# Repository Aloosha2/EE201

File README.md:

# EE 201

This is contains all of my content for lab 8: arduometer

***NOTE: my voltage divider was faulty so I asked Pranav how to proceed with assignment. After many tests and checks, my board would not connect to the arduino and code would not upload. Pranav and Sushree said the board was too damaged so I should just proceed with building the case. Thus, here are the photos in the branch.

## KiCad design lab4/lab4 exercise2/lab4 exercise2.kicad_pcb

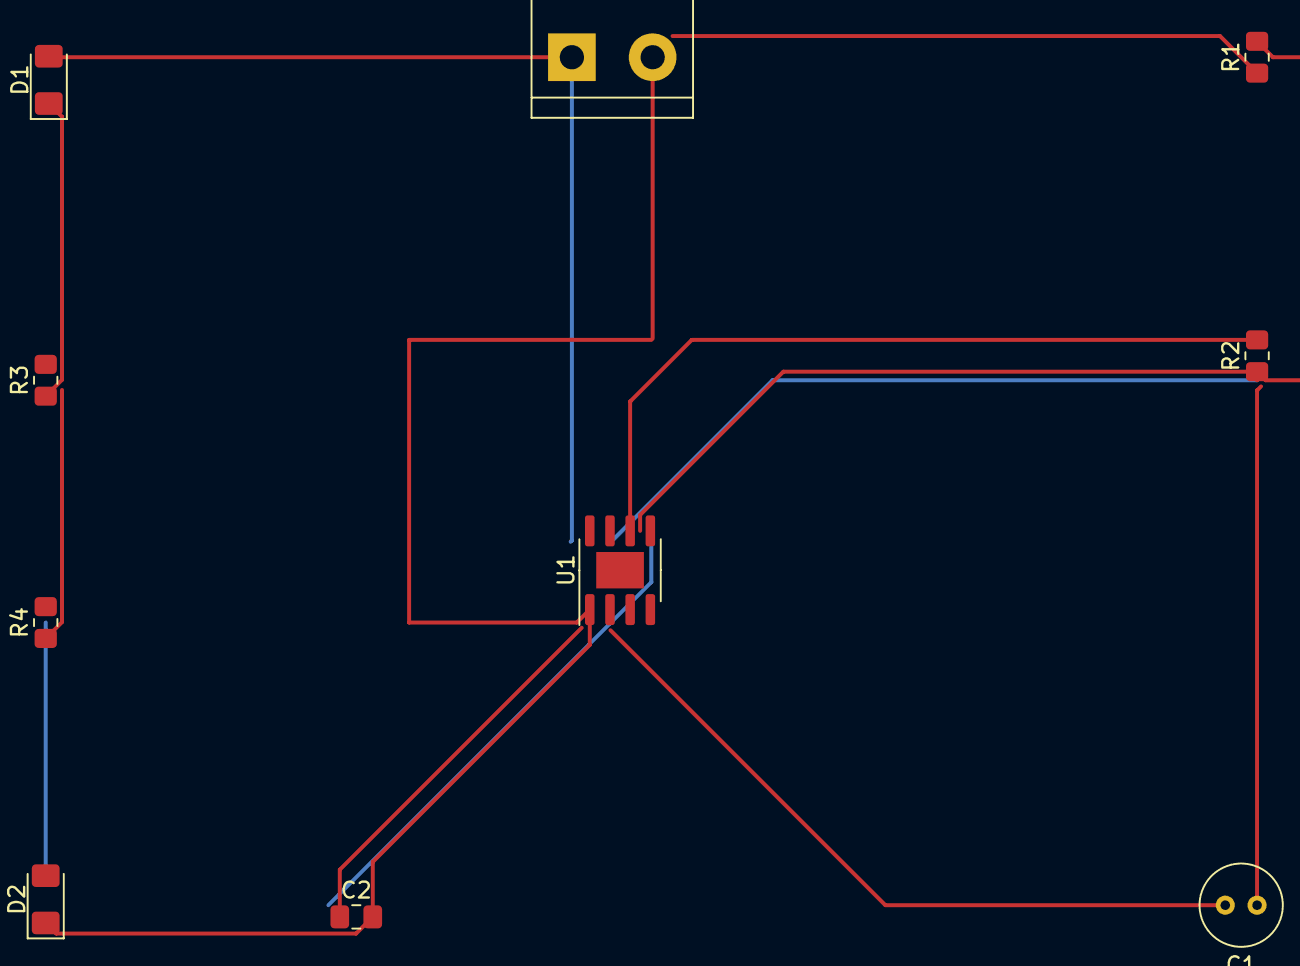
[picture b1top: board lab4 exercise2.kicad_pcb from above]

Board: 2 copper layers, 10 parts (0 on the bottom side), 8 nets.

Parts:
C1: 10 µF; C_Radial_D5.0mm_H5.0mm_P2.00mm
C2: 0.01µF; C_0805_2012Metric_Pad1.18x1.45mm_HandSolder
D1, D2: LED; LED_1206_3216Metric_Pad1.42x1.75mm_HandSolder
J1: Conn_01x02_Male; TerminalBlock_bornier-2_P5.08mm
R1, R3, R4: 1k; R_0805_2012Metric_Pad1.20x1.40mm_HandSolder
R2: 10k; R_0805_2012Metric_Pad1.20x1.40mm_HandSolder
U1: NE555D; SOIC-8-1EP_3.9x4.9mm_P1.27mm_EP2.29x3mm

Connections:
+9V: D1.2 (A), J1.1, R1.1, U1.8 (VCC)
GND: C1.2, C2.2, D2.1 (K), J1.2, U1.1 (GND)
unnamed: C1.1, R2.2, U1.6 (THR)
unnamed: C2.1, U1.5 (CV)
unnamed: D1.1 (K), R3.1
unnamed: D2.2 (A), R4.2
unnamed: R1.2, R2.1, U1.7 (DIS)
unnamed: R3.2, R4.1

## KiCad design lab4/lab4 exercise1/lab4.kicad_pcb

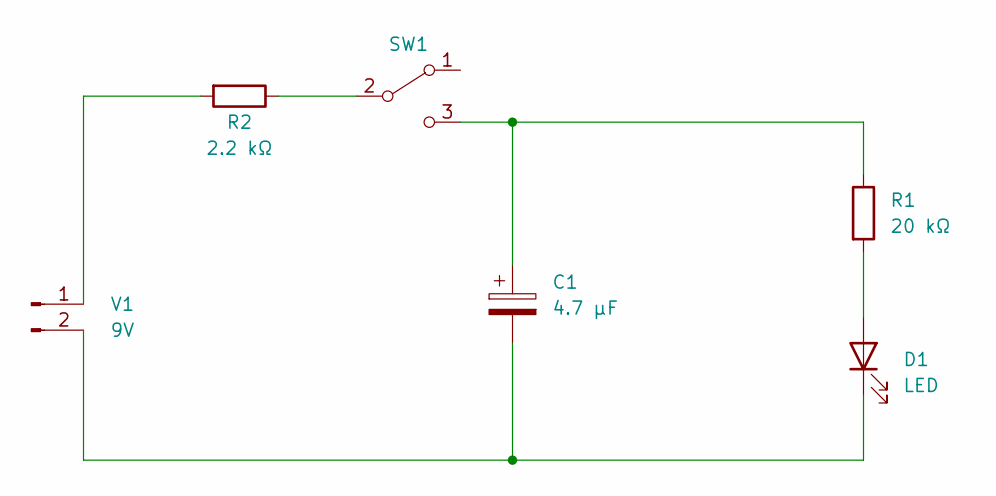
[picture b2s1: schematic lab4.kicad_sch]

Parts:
C1: 4.7 µF; C_Radial_D5.0mm_H5.0mm_P2.00mm
D1: LED; LED_D5.0mm
R1: 20 kΩ; R_Axial_DIN0516_L15.5mm_D5.0mm_P20.32mm_Horizontal
R2: 2.2 kΩ; R_Axial_DIN0516_L15.5mm_D5.0mm_P20.32mm_Horizontal
SW1: s; SW_E-Switch_EG1224_SPDT_Angled
V1: 9V; JST_PH_B2B-PH-K_1x02_P2.00mm_Vertical

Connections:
unnamed: C1.1, R1.1, SW1.3 (C)
unnamed: C1.2, D1.1 (K), V1.2
unnamed: D1.2 (A), R1.2
unnamed: R2.1, SW1.2 (B)
unnamed: R2.2, V1.1

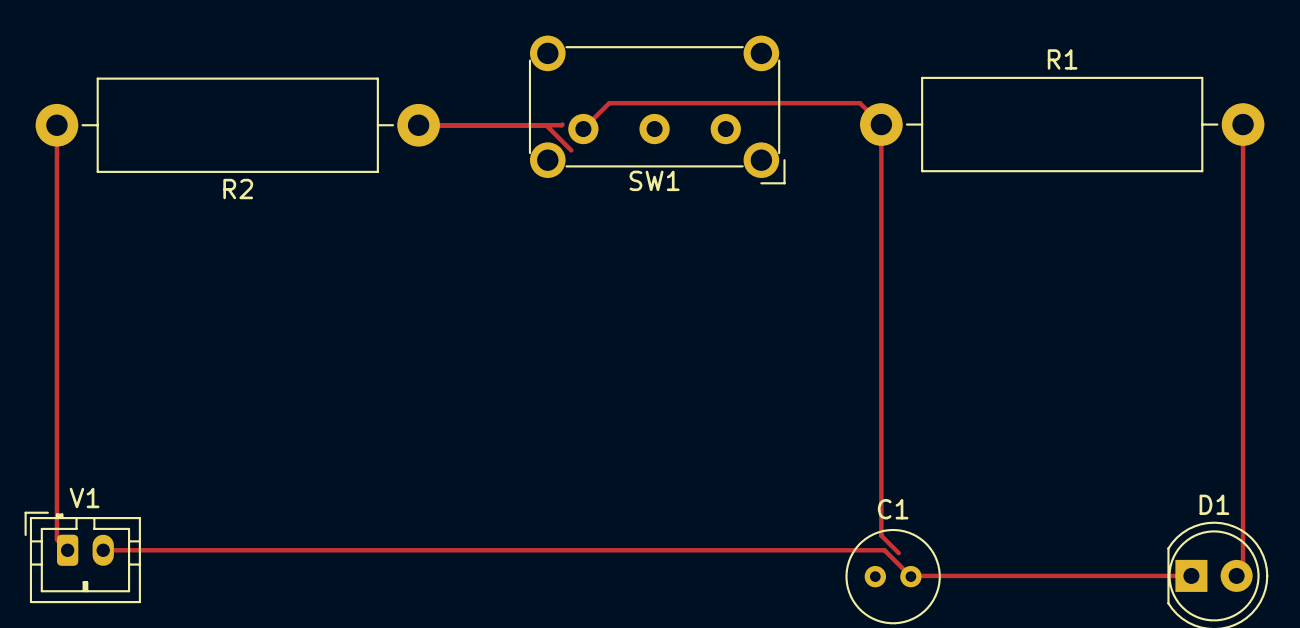
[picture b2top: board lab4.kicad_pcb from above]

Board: 2 copper layers, 6 parts (0 on the bottom side), 5 nets.

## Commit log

2023-01-10 Created the heading
2023-01-10 Adding name.txt
2023-01-10 added a second line
2023-01-10 added aboutMe
2023-01-10 added file
2023-01-10 add readme
2023-01-10 updated readme file
2023-01-10 added photo
2023-01-11 updated final readMe
2023-01-11 Adding a file.
2023-01-19 created new branch
2023-01-19 added lab1
2023-01-19 added Arduino exercises
2023-01-24 added read me file to lab 4
2023-01-24 added files
2023-01-24 added lab4
2023-01-24 lab4 work
2023-01-24 lab 4 work
2023-01-31 uploaded photos
2023-01-31 removed lab4
2023-02-01 added soldering photos
2023-02-07 updated lab4 from lab6 instructions
2023-02-07 lab6 work on lab4
2023-02-14 created gerber files
2023-02-14 added gerber files
2023-03-09 Updated lab 4 pcb layout
2023-03-10 Create lab 8 content
